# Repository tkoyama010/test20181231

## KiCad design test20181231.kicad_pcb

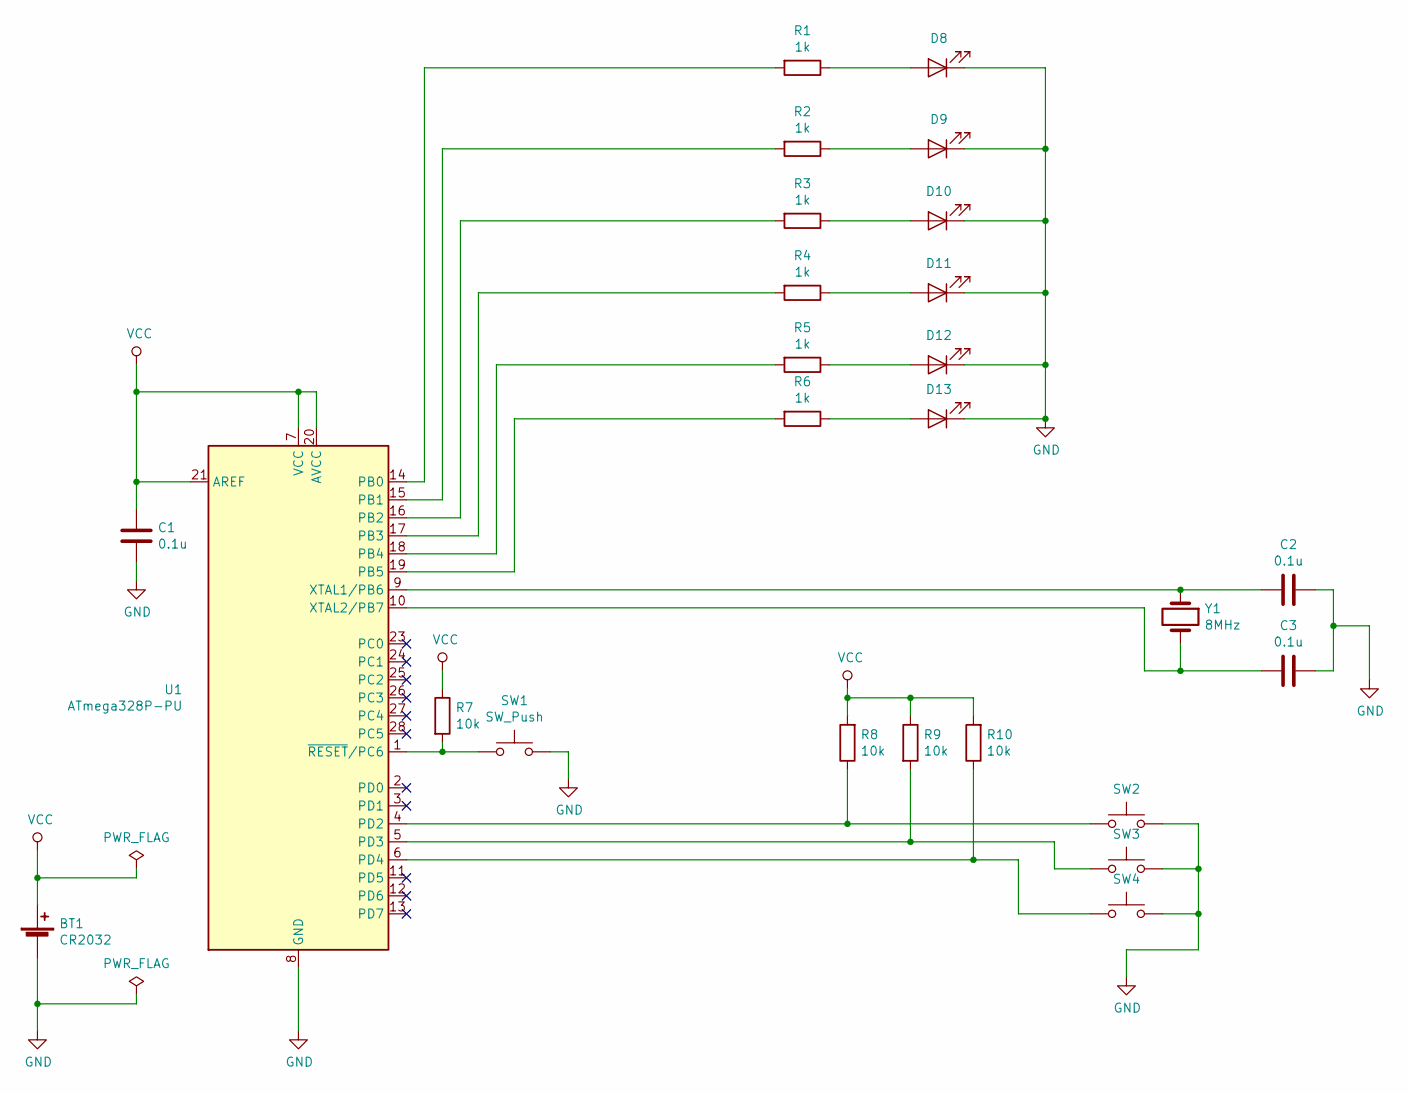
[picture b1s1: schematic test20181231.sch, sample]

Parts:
BT1: CR2032; P-06925_20181231
C1, C2, C3: 0.1u; C_Disc_D3.4mm_W2.1mm_P2.50mm
D8, D9, D10, D11, D12, D13: LED; LED_D5.0mm
R1, R2, R3, R4, R5, R6: 1k; R_Axial_DIN0207_L6.3mm_D2.5mm_P7.62mm_Horizontal
R7, R8, R9, R10: 10k; R_Axial_DIN0207_L6.3mm_D2.5mm_P7.62mm_Horizontal
SW1, SW2, SW3, SW4: SW_Push; SW_PUSH_6mm
U1: ATmega328P-PU; DIP-28_W7.62mm_LongPads
Y1: 8MHz; Crystal_HC49-4H_Vertical

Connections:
GND: BT1.2 (-), C1.2, C2.1, C3.1, D8.1 (K), D9.1 (K), D10.1 (K), D11.1 (K), D12.1 (K), D13.1 (K), SW1.2, SW2.2, SW3.2, SW4.2, U1.8 (GND), U1.22 (GND)
unnamed: C2.2, U1.9 (XTAL1/PB6), Y1.1
unnamed: C3.2, U1.10 (XTAL2/PB7), Y1.2
unnamed: D8.2 (A), R1.1
unnamed: D9.2 (A), R2.1
unnamed: D10.2 (A), R3.1
unnamed: D11.2 (A), R4.1
unnamed: D12.2 (A), R5.1
unnamed: D13.2 (A), R6.1
unnamed: R1.2, U1.14 (PB0)
unnamed: R2.2, U1.15 (PB1)
unnamed: R3.2, U1.16 (PB2)
unnamed: R4.2, U1.17 (PB3)
unnamed: R5.2, U1.18 (PB4)
unnamed: R6.2, U1.19 (PB5)
unnamed: R7.2, SW1.1, U1.1 (~RESET~/PC6)
unnamed: R8.1, SW2.1, U1.4 (PD2)
unnamed: R9.2, SW3.1, U1.5 (PD3)
unnamed: R10.1, SW4.1, U1.6 (PD4)
VCC: BT1.1 (+), C1.1, R7.1, R8.2, R9.1, R10.2, U1.7 (VCC), U1.20 (AVCC), U1.21 (AREF)

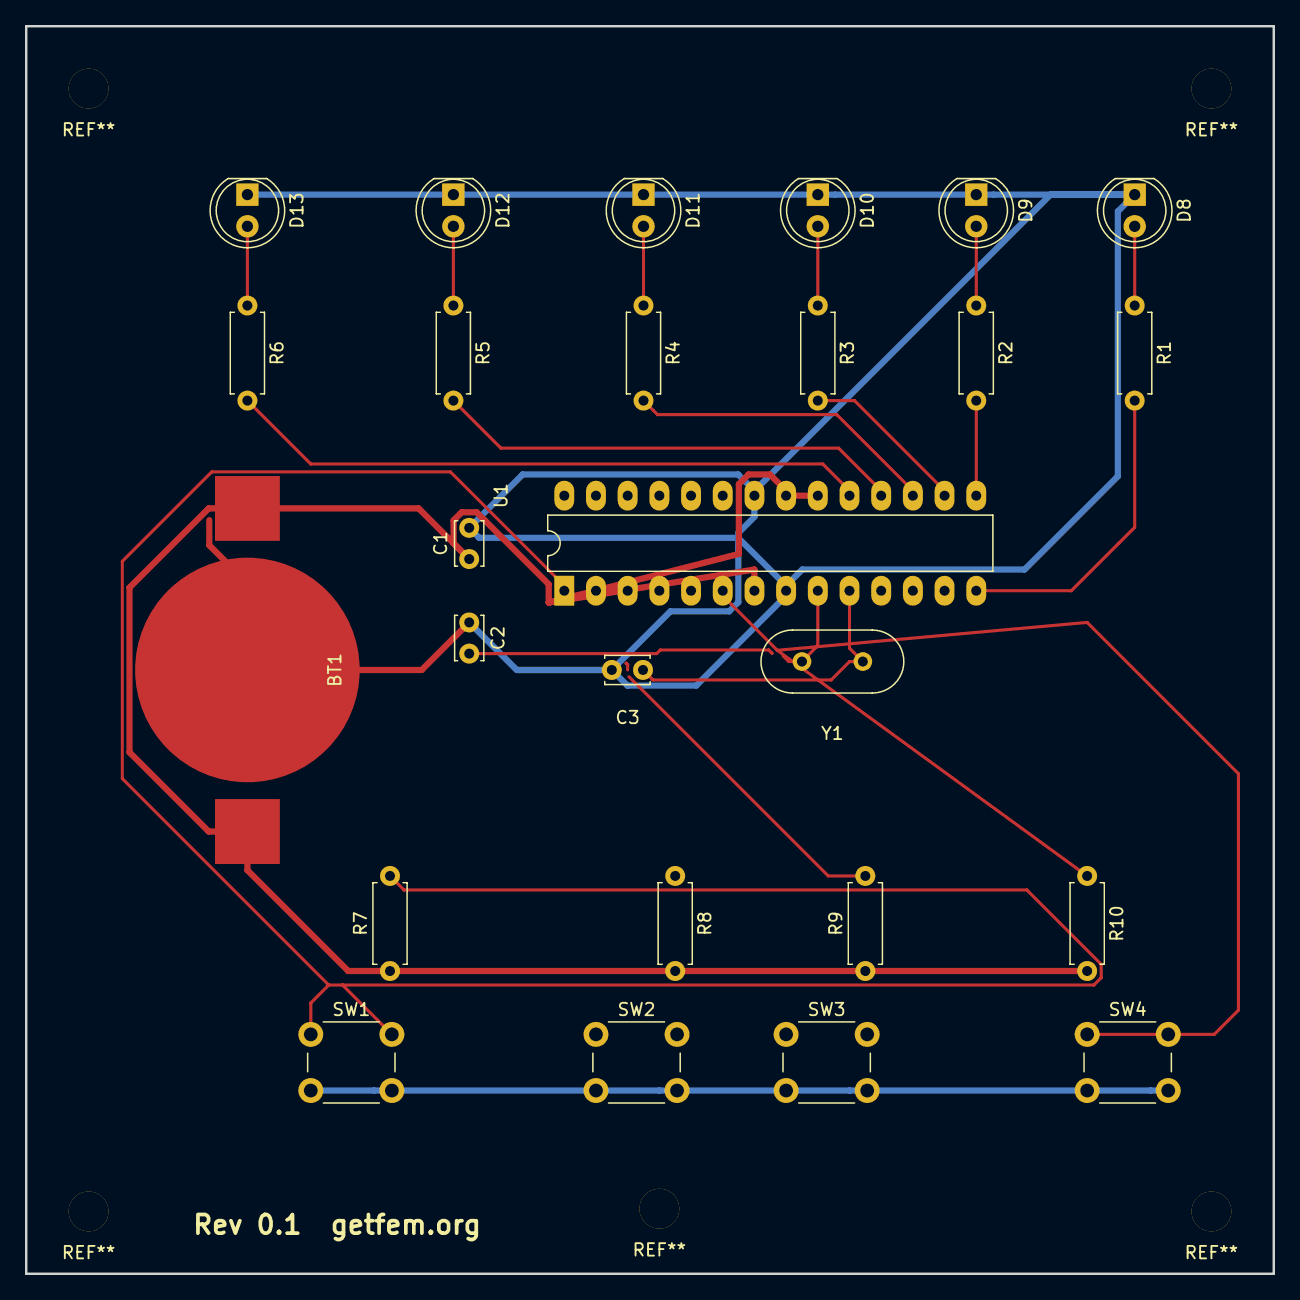
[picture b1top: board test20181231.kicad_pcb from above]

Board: 2 copper layers, 100.0 x 100.0 mm, 26 parts (0 on the bottom side), 20 nets.
